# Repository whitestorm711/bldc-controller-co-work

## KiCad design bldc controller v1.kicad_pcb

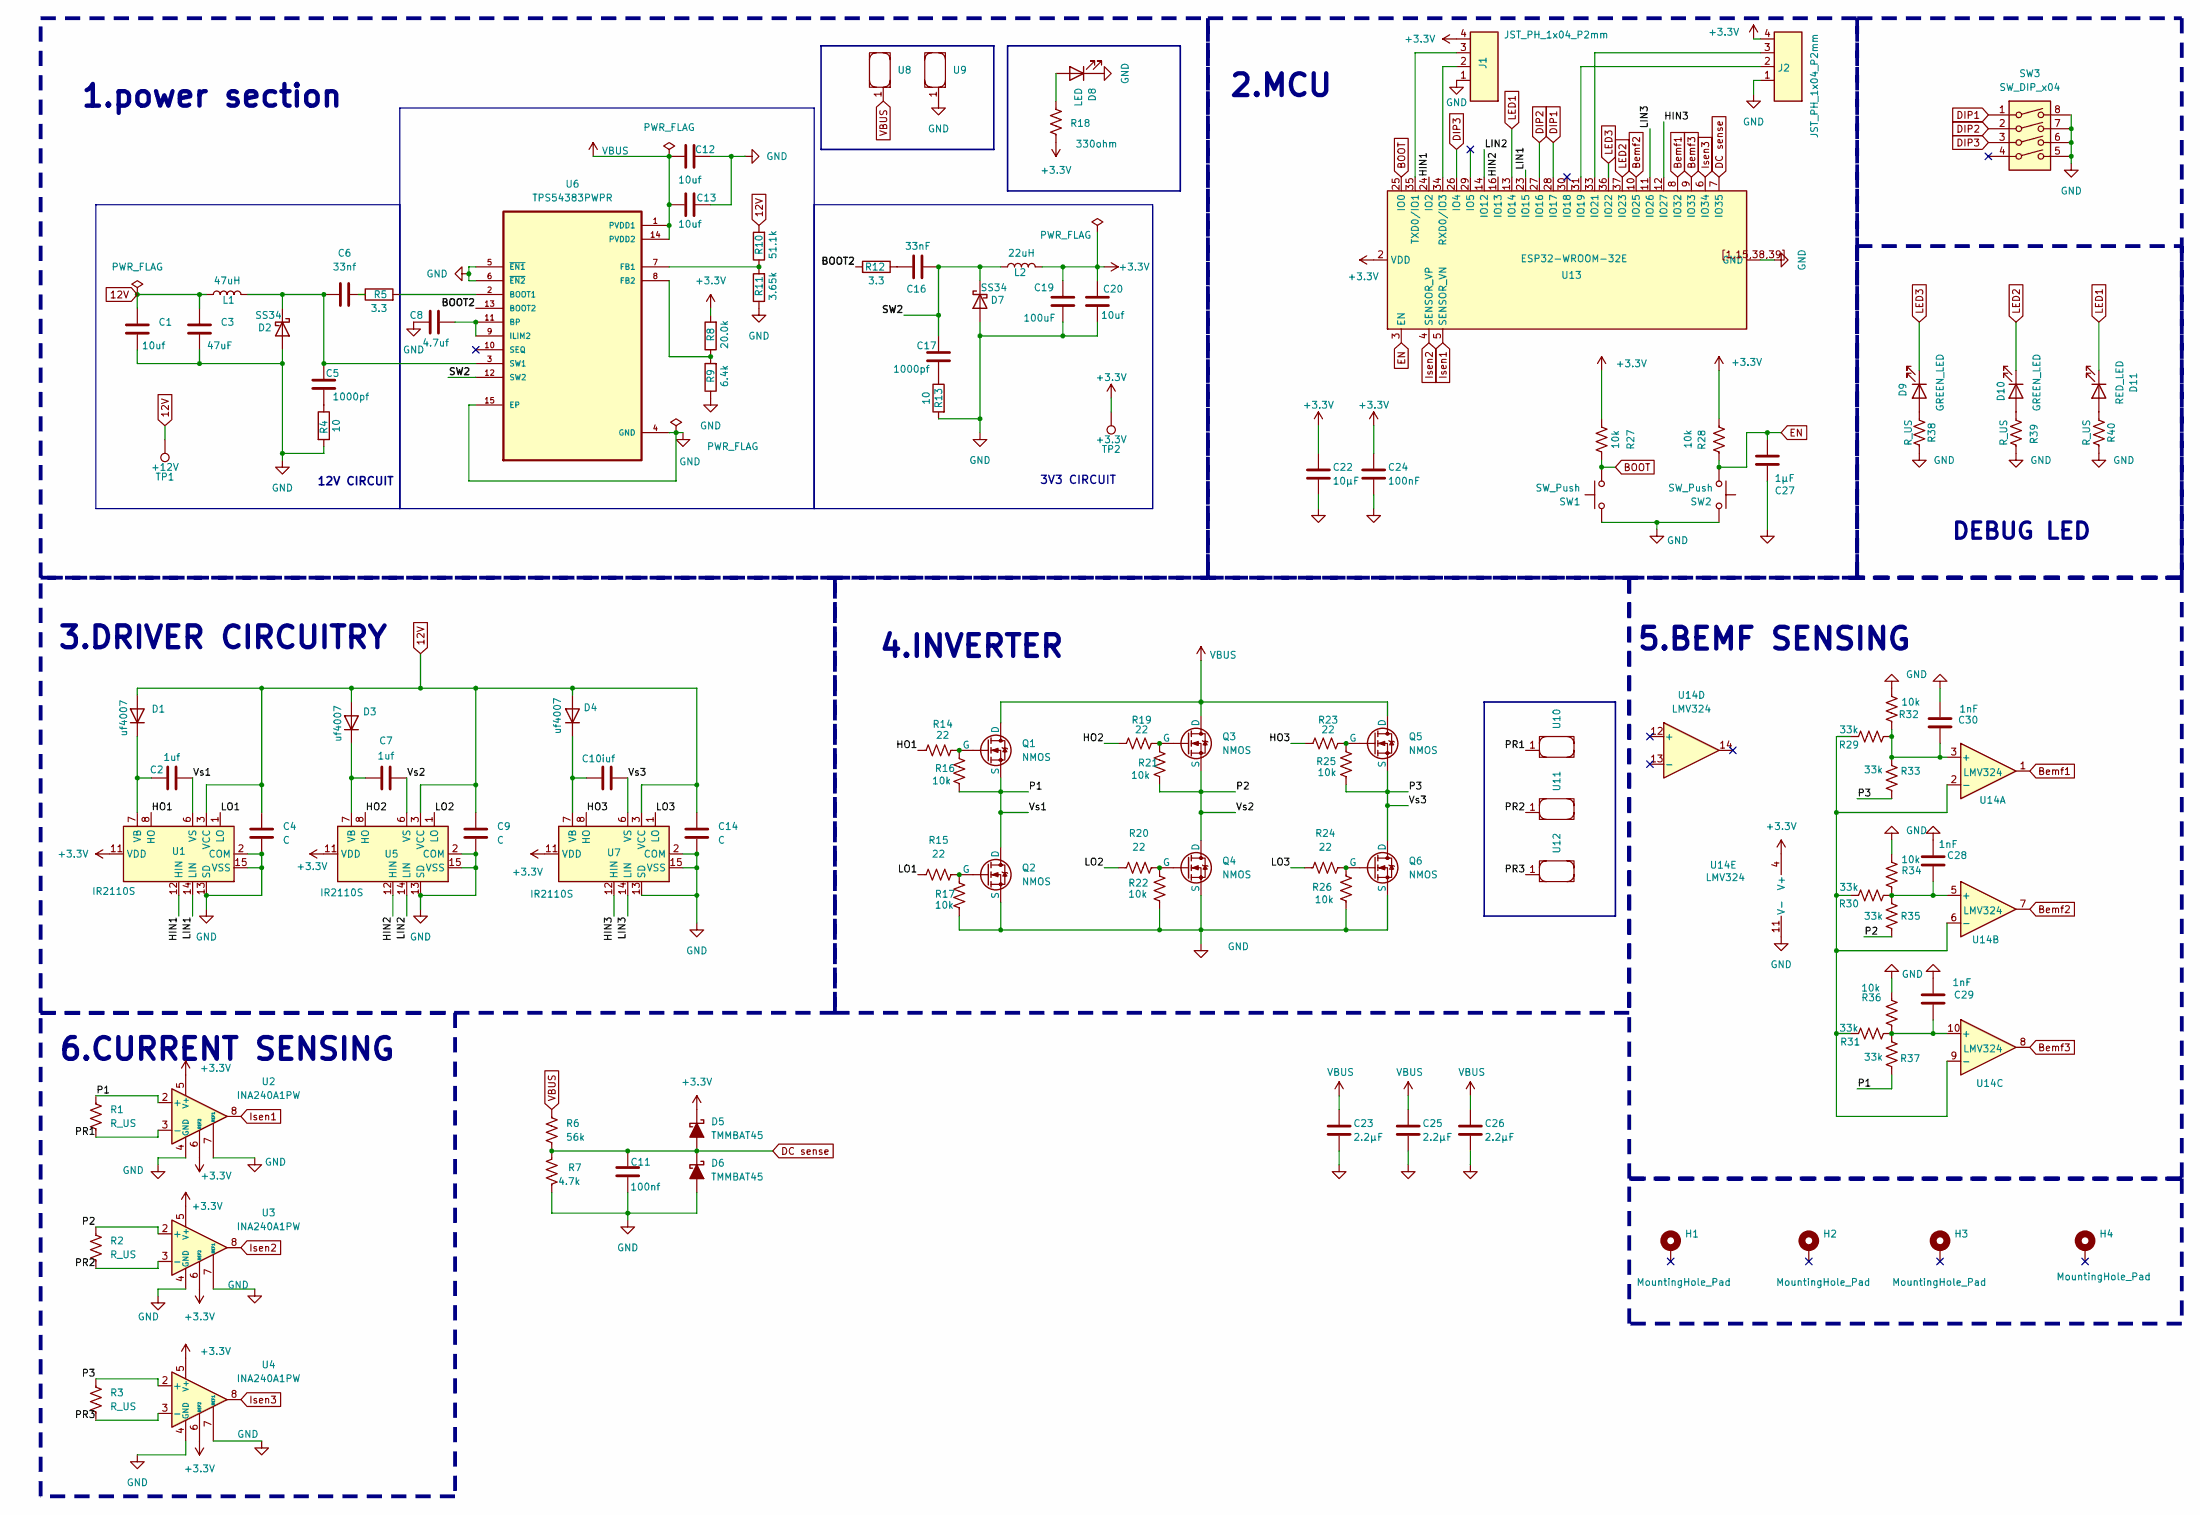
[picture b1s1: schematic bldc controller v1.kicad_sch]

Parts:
C1, C12, C13, C20: 10uf; C_1210_3225Metric
C2, C7: 1uf; C_1206_3216Metric
C3: 47uF; CP_Elec_8x10
C4, C9, C14: C; C_0805_2012Metric
C5, C17: 1000pf; C_0805_2012Metric
C6: 33nf; C_0805_2012Metric
C8: 4.7uf; C_1206_3216Metric
C10: iuf; C_1206_3216Metric
C11: 100nf; C_0805_2012Metric_Pad1.18x1.45mm_HandSolder
C16: 33nF; C_0805_2012Metric
C19: 100uF; CP_Elec_8x10
C22: 10µF; C_0805_2012Metric
C23, C25, C26: 2.2µF; C_1210_3225Metric
C24: 100nF; C_0603_1608Metric
C27: 1µF; C_0603_1608Metric
C28, C29, C30: 1nF; C_0603_1608Metric
D1, D3, D4: uf4007; D_1206_3216Metric_Pad1.42x1.75mm_HandSolder
D2, D7: SS34; D_SMA
D5, D6: TMMBAT45; D_MiniMELF
D8: LED; LED_1206_3216Metric
D9, D10: GREEN_LED; LED_1206_3216Metric
D11: RED_LED; LED_1206_3216Metric
H1, H2, H3, H4: MountingHole_Pad; MountingHole_3.2mm_M3_DIN965_Pad
J1, J2: JST_PH_1x04_P2mm; JST_PH_S4B-PH-SM4-TB_1x04-1MP_P2.00mm_Horizontal
L1: 47uH; L_Coilcraft_XAL7030-152
L2: 22uH; L_Coilcraft_XAL7030-152
Q1, Q2, Q3, Q4, Q5, Q6: NMOS; TO-263-2
R1, R2, R3: R_US; R_2512_6332Metric_Pad1.40x3.35mm_HandSolder
R4, R13: 10; R_0805_2012Metric
R5, R12: 3.3; R_0805_2012Metric
R6: 56k; R_0805_2012Metric
R7: 4.7k; R_0805_2012Metric
R8: 20.0k; R_0805_2012Metric
R9: 6.4k; R_0805_2012Metric
R10: 51.1k; R_0805_2012Metric
R11: 3.65k; R_0805_2012Metric
R14, R15, R19, R20, R23, R24: 22; R_0805_2012Metric
R16, R17, R21, R22, R25, R26, R27, R28, R32, R34, R36: 10k; R_0805_2012Metric
R18: 330ohm; R_0805_2012Metric
R29, R30, R31, R33, R35, R37: 33k; R_0805_2012Metric
R38, R39, R40: R_US; R_0805_2012Metric
SW1, SW2: SW_Push; SW_Push_1P1T_NO_CK_KMR2
SW3: SW_DIP_x04; SW_DIP_SPSTx04_Slide_6.7x11.72mm_W8.61mm_P2.54mm_LowProfile
TP1: +12V; TestPoint_Pad_D1.5mm
TP2: +3.3V; TestPoint_Pad_D1.5mm
U1, U5, U7: IR2110S; SOIC-16W_7.5x10.3mm_P1.27mm
U2, U3, U4: INA240A1PW; TSSOP-8_4.4x3mm_P0.65mm
U6: TPS54383PWPR; TSSOP-14-1EP_4.4x5mm_P0.65mm
U8, U9, U10, U11, U12: Untitled
U13: ESP32-WROOM-32E
U14: LMV324; SOIC-14_3.9x8.7mm_P1.27mm

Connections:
12V: C1.1, C3.1, C4.1, C9.1, C14.1, D1.2 (A), D3.2 (A), D4.2 (A), L1.1, R10.2, TP1.1, U1.3 (VCC), U5.3 (VCC), U7.3 (VCC); also elsewhere on the board
+3.3V: C19.1, C20.1, C22.1, C24.1, D5.1 (K), J1.4, J2.4, L2.1, R8.2, R18.2, R27.2, R28.2, TP2.1, U1.11 (VDD), U2.5 (V+), U2.6 (REF2), U3.5 (V+), U3.6 (REF2), U4.5 (V+), U4.6 (REF2), U5.11 (VDD), U7.11 (VDD), U13.2 (VDD), U14.4 (V+); also elsewhere on the board
/BOOT2: R12.2, U6.13 (BOOT2)
/HIN1: U1.12 (HIN), U13.24 (IO2)
/HIN2: U5.12 (HIN), U13.16 (IO13)
/HIN3: U7.12 (HIN), U13.12 (IO27)
/HO1: R14.1, U1.8 (HO)
/HO2: R19.1, U5.8 (HO)
/HO3: R23.1, U7.8 (HO)
/LIN1: U1.14 (LIN), U13.23 (IO15)
/LIN2: U5.14 (LIN), U13.14 (IO12)
/LIN3: U7.14 (LIN), U13.11 (IO26)
/LO1: R15.1, U1.1 (LO)
/LO2: R20.1, U5.1 (LO)
/LO3: R24.1, U7.1 (LO)
/P1: C2.2, Q1.3 (S), Q2.2 (D), R1.1, R16.1, R37.2, U1.6 (VS), U2.2 (+)
/P2: C7.2, Q3.3 (S), Q4.2 (D), R2.1, R21.1, R35.2, U3.2 (+), U5.6 (VS)
/P3: C10.2, Q5.3 (S), Q6.2 (D), R3.1, R25.1, R33.2, U4.2 (+), U7.6 (VS)
/PR1: R1.2, U2.3 (-), U10.1
/PR2: R2.2, U3.3 (-), U11.1
/PR3: R3.2, U4.3 (-), U12.1
/SW2: C16.1, C17.1, D7.1 (K), L2.2, U6.12 (SW2)
BOOT: R27.1, SW1.2, U13.25 (IO0)
Bemf1: U13.8 (IO32), U14.1
Bemf2: U13.10 (IO25), U14.7
Bemf3: U13.9 (IO33), U14.8
DC sense: C11.1, D5.2 (A), D6.1 (K), R6.2, R7.1, U13.7 (IO35)
DIP1: SW3.1, U13.28 (IO17)
DIP2: SW3.2, U13.27 (IO16)
DIP3: SW3.3, U13.26 (IO4)
EN: C27.1, R28.1, SW2.1, U13.3 (EN)
GND: C1.2, C3.2, C4.2, C8.1, C9.2, C11.2, C12.2, C13.2, C14.2, C19.2, C20.2, C22.2, C23.2, C24.2, C25.2, C26.2, C27.2, C28.2, C29.2, C30.2, D2.2 (A), D6.2 (A), D7.2 (A), D8.1 (K), J1.1, J2.1, Q2.3 (S), Q4.3 (S), Q6.3 (S), R4.2, R7.2, R9.1, R11.1, R13.2, R17.1, R22.1, R26.1, R32.1, R34.1, R36.1, R38.2, R39.2, R40.2, SW1.1, SW2.2, SW3.5, SW3.6, SW3.7, SW3.8, U1.2 (COM), U1.13 (SD), U1.15 (VSS), U2.1 (GND), U2.4 (GND), U2.7 (REF1), U3.1 (GND), U3.4 (GND), U3.7 (REF1), U4.1 (GND), U4.4 (GND), U4.7 (REF1), U5.2 (COM), U5.13 (SD), U5.15 (VSS), U6.4 (GND), U6.5 (~EN1), U6.6 (~EN2), U6.15 (EP), U7.2 (COM), U7.13 (SD), U7.15 (VSS), U9.1, U13.1 (GND), U13.15 (GND), U13.38 (GND), U13.39 (GND), U13.[1,15,38,39] (GND), U14.11 (V-)
Isen1: U2.8, U13.5 (SENSOR_VN)
Isen2: U3.8, U13.4 (SENSOR_VP)
Isen3: U4.8, U13.6 (IO34)
LED1: D11.1 (K), U13.13 (IO14); also elsewhere on the board
LED2: D10.1 (K), U13.37 (IO23)
LED3: D9.1 (K), U13.36 (IO22)
unnamed: C5.2, R4.1
unnamed: C6.2, R5.1
unnamed: C16.2, R12.1
unnamed: C17.2, R13.1
unnamed: C2.1, D1.1 (K), U1.7 (VB)
unnamed: C5.1, C6.1, D2.1 (K), L1.2, U6.3 (SW1)
unnamed: C7.1, D3.1 (K), U5.7 (VB)
unnamed: C10.1, D4.1 (K), U7.7 (VB)
unnamed: D8.2 (A), R18.1
unnamed: D9.2 (A), R38.1
unnamed: D10.2 (A), R39.1
unnamed 49: D11.2 (A), R40.1; also elsewhere on the board
unnamed: Q1.1 (G), R14.2, R16.2
unnamed: Q2.1 (G), R15.2, R17.2
unnamed: Q3.1 (G), R19.2, R21.2
unnamed: Q4.1 (G), R20.2, R22.2
unnamed: Q5.1 (G), R23.2, R25.2
unnamed: Q6.1 (G), R24.2, R26.2
unnamed: R5.2, U6.2 (BOOT1)
unnamed: C8.2, U6.9 (ILIM2), U6.11 (BP)
unnamed: R10.1, R11.2, U6.7 (FB1)
unnamed: R8.1, R9.2, U6.8 (FB2)
unnamed: J2.2, U13.31 (IO19)
unnamed: J2.3, U13.33 (IO21)
unnamed: J1.2, U13.34 (RXD0/IO3)
unnamed: J1.3, U13.35 (TXD0/IO1)
unnamed: C30.1, R29.1, R32.2, R33.1, U14.3 (+)
unnamed: R29.2, R30.2, R31.2, U14.2 (-), U14.6 (-), U14.9 (-)
unnamed: C28.1, R30.1, R34.2, R35.1, U14.5 (+)
unnamed: C29.1, R31.1, R36.2, R37.1, U14.10 (+)
VBUS: C12.1, C13.1, C23.1, C25.1, C26.1, Q1.2 (D), Q3.2 (D), Q5.2 (D), R6.1, U6.1 (PVDD1), U6.14 (PVDD2), U8.1

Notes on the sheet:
3.DRIVER CIRCUITRY
5.BEMF SENSING
12V CIRCUIT
2.MCU
3V3 CIRCUIT
4.INVERTER
1.power section
DEBUG LED
6.CURRENT SENSING

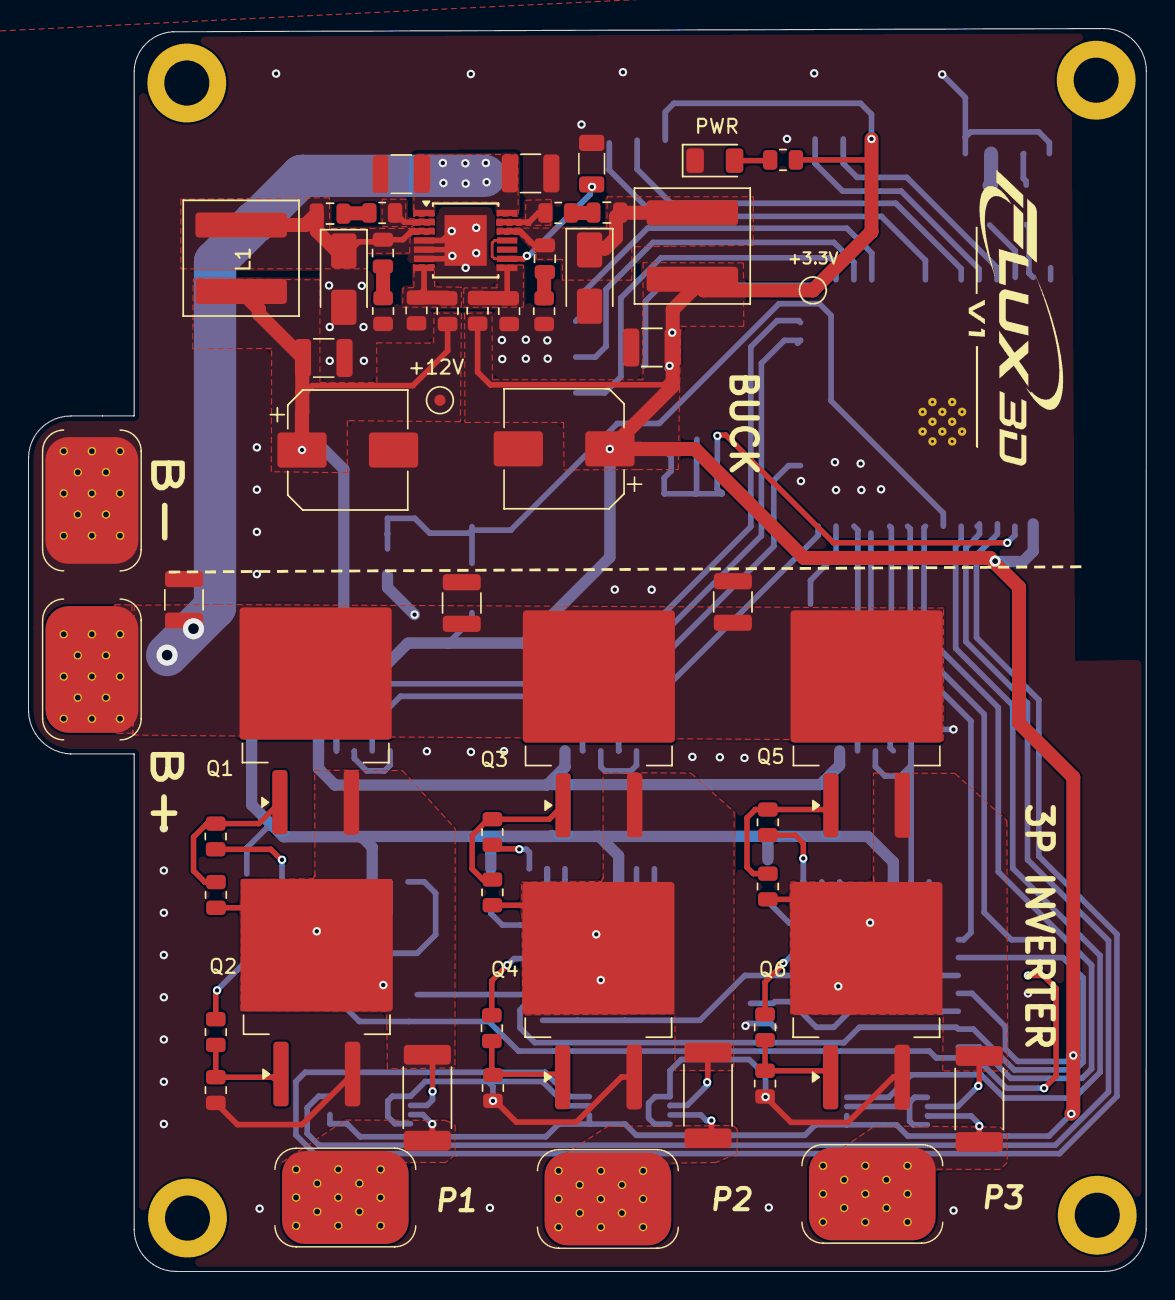
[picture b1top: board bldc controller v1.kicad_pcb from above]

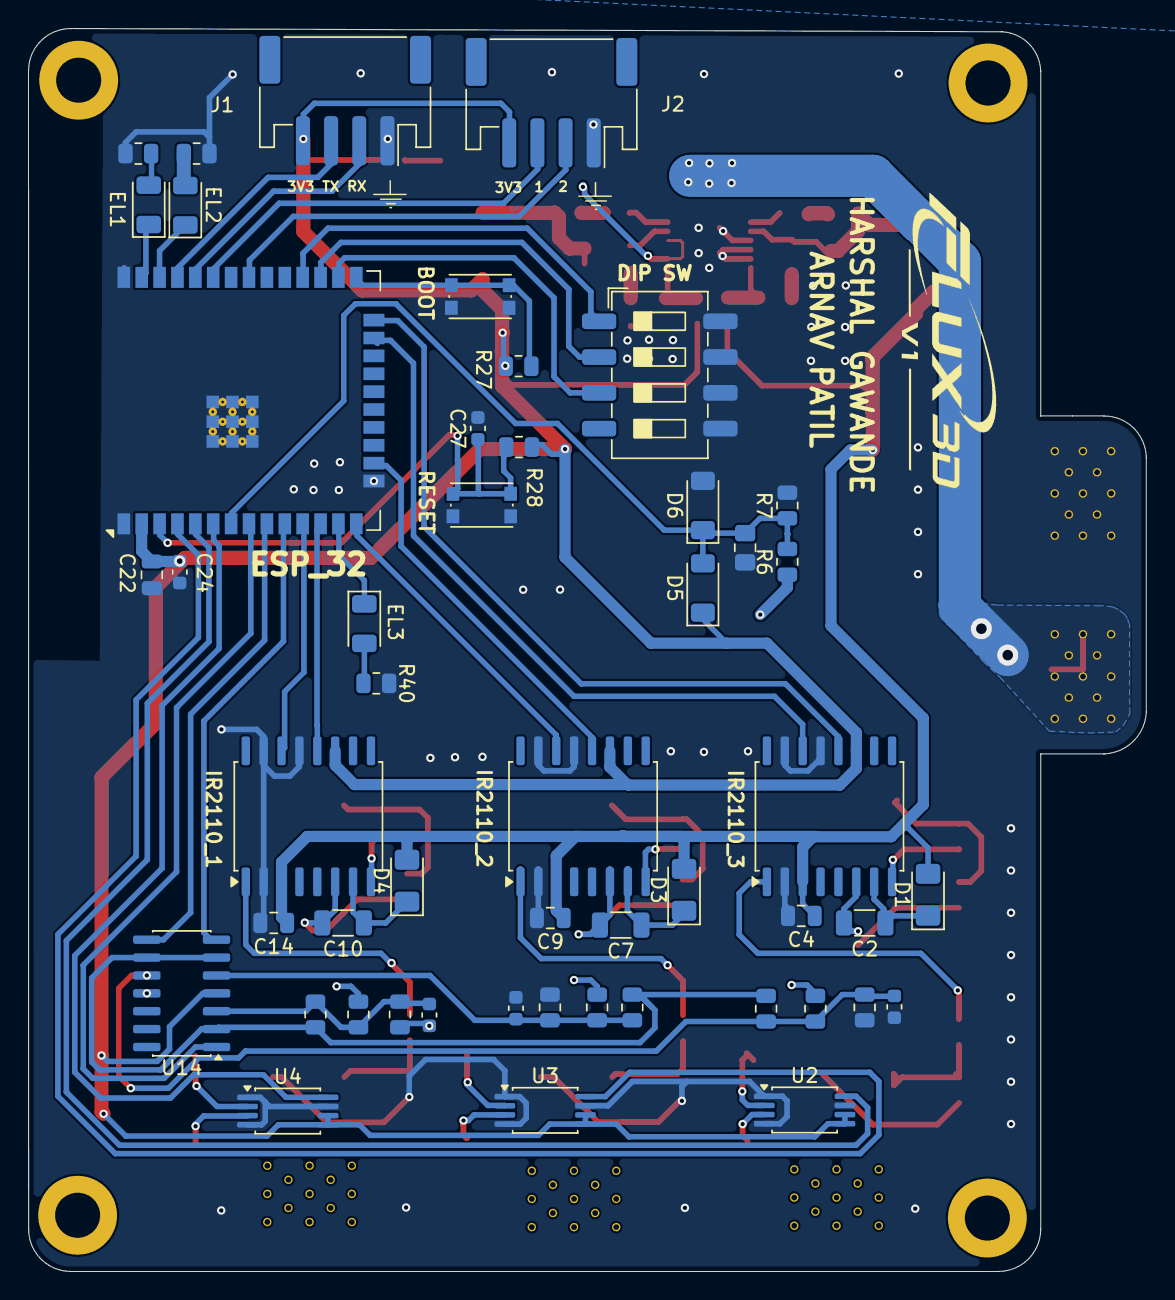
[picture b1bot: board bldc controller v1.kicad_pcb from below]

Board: 2 copper layers, 79.4 x 88.3 mm, 111 parts (50 on the bottom side), 69 nets.

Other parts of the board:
+3.3V: +3.3V; TestPoint_Pad_D1.5mm
+12V: +12V; TestPoint_Pad_D1.5mm
EL3: RED_LED; LED_1206_3216Metric

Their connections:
12V: +12V.1 (1_1); also elsewhere on the board
+3.3V: +3.3V.1 (1_1); also elsewhere on the board
LED1: EL3.1 (K); also elsewhere on the board
unnamed 49: EL3.2 (A); also elsewhere on the board
